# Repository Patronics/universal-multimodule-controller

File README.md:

# Universal Multi-Module Controller

This project aims to allow standard input devices (such as game controllers and keyboards) to control output to 4-in-one multi-module transmitters.

Created by Patrick Leiser and Josh Adriano.

## Installation
Use the [Arduino-Pico board core](https://arduino-pico.readthedocs.io/en/latest/) by Earle Philhower
Dependencies:
U8g2 by oliver
ArduinoJson by Benoit Blanchon
Bounce2 by Thomas O Fredericks
Pico PIO USB by Sekigon-gonnoc

You can program it with the Arduino IDE directly, adjust the menu options as described at the top of `GamesteerRC.ino`.

Alternatively, for advanced usage and debugging, you can install the [Arduino-CLI](https://docs.arduino.cc/arduino-cli/) and use the scripts as described below: 

## Build & Debug Scripts

---

### build.sh  
Builds a **release version** of the firmware using Arduino CLI.

- Optimized for performance (`-O2` / `-Os`)
- Produces `.elf` and `.uf2` in `build/`
- Use when you want final or production-like firmware

---

### debug-build.sh  
Builds a **debug version** of the firmware.

- Uses `-Og` optimization for good debugging behavior
- Includes full debug symbols (`-g`)
- Outputs to `build-debug/`
- Use when stepping through code or inspecting variables with GDB

---

### flash.sh  
Flashes firmware using the **Raspberry Pi Debug Probe (OpenOCD + SWD)**.

- Programs the `.elf` directly to flash
- Verifies and resets the device
- Use for fast iteration during debugging

---

### openocd.sh  
Starts the **OpenOCD GDB server**.

- Provides a debugging connection on port 3333
- Required before connecting GDB
- Use when preparing a debug session

---

### gdb.sh  
Launches **GDB for source-level debugging**.

- Connects to OpenOCD (`localhost:3333`)
- Uses the project `.elf`
- Use for breakpoints, stepping, and inspecting state
- See debugging section below for additional details
---

### upload.sh  
Flashes firmware using the **UF2 bootloader (USB mode)**.
- uses `arduino-cli upload`
- Before use, edit upload.sh with the port of your target device, such as `/dev/cu.usbmodem101` or `COM7`
  - Alternatively, you can manually boot the device into BOOTSEL mode, and copy `build/GamesteerRC.ino.uf2` onto the device.
- No debugger needed
- Use for simple deployment or recovery
---

### Typical usage
Call the scripts from the top level of the directory, such as `./scripts/build.sh`
- **Development (debugging):** `debug-build.sh` → `flash.sh` → `openocd.sh` → *(in a second terminal session)* `gdb.sh`
- **Quick standalone flash:** `build.sh → upload.sh`

## Debugging
For debugging, once OpenOCD and GDB are active, within GDB run 
```gdb
target extended-remote :3333
monitor reset halt
break panic
continue

```

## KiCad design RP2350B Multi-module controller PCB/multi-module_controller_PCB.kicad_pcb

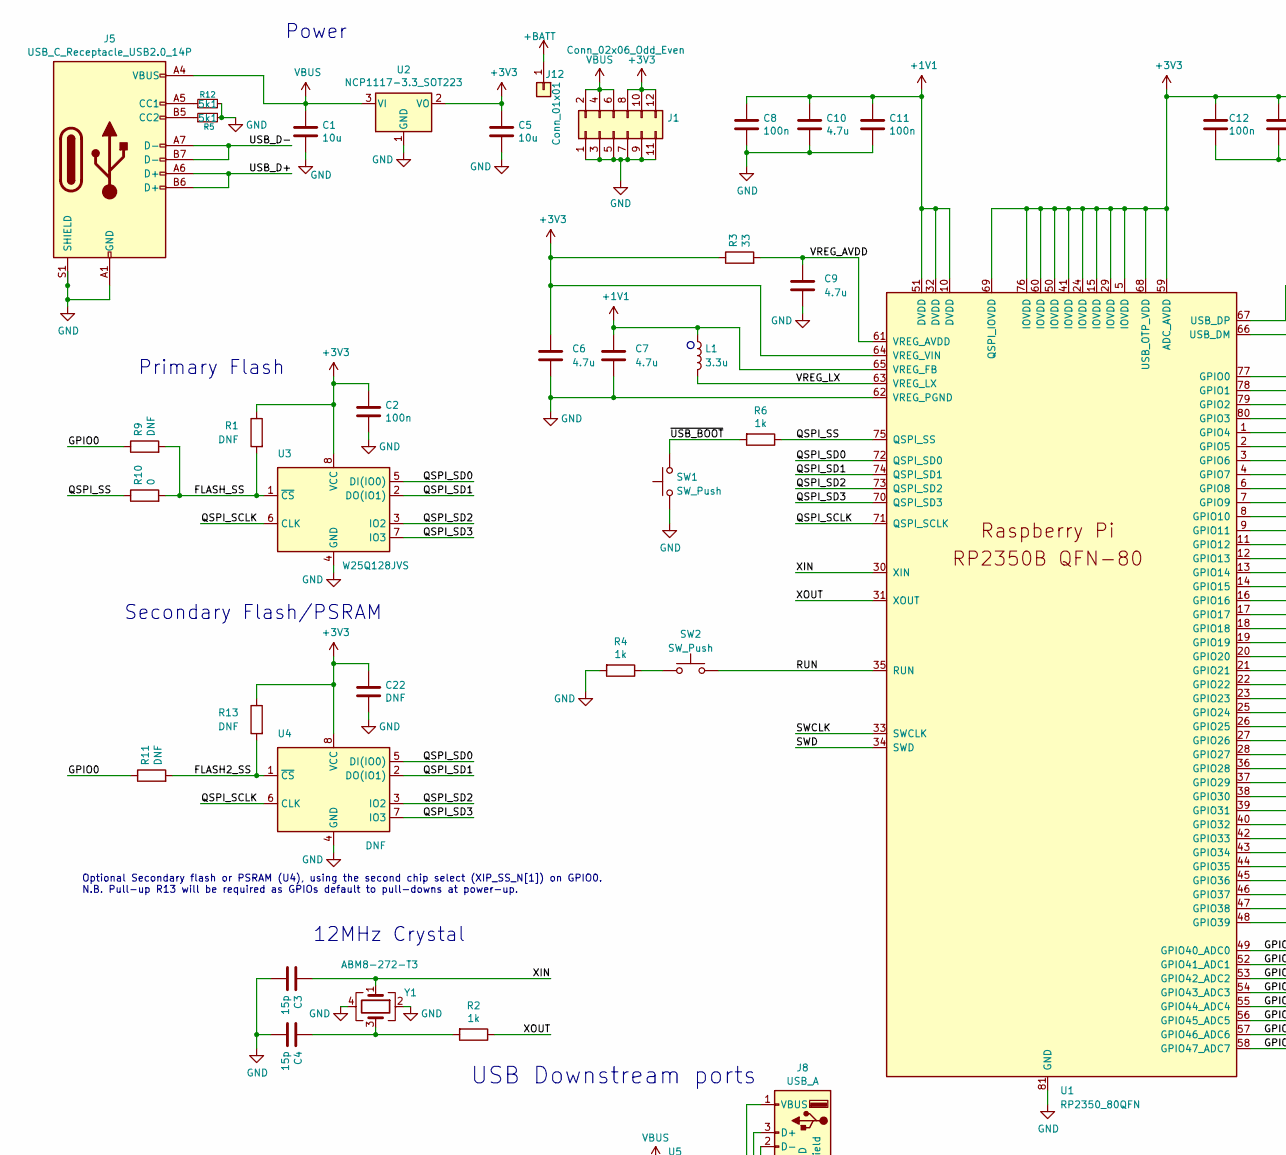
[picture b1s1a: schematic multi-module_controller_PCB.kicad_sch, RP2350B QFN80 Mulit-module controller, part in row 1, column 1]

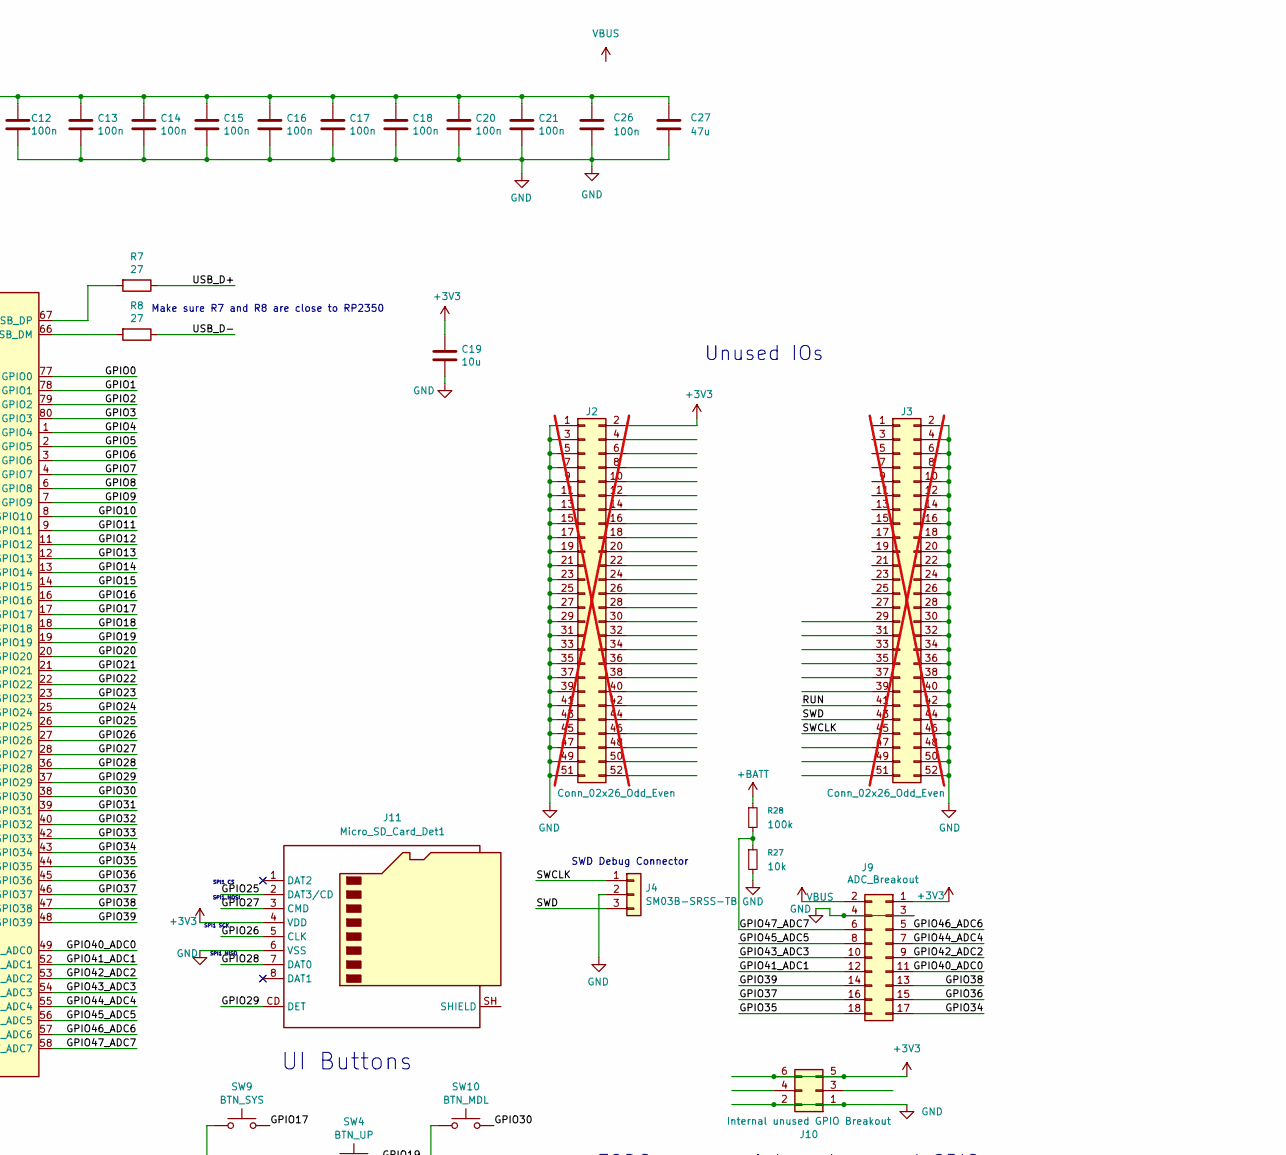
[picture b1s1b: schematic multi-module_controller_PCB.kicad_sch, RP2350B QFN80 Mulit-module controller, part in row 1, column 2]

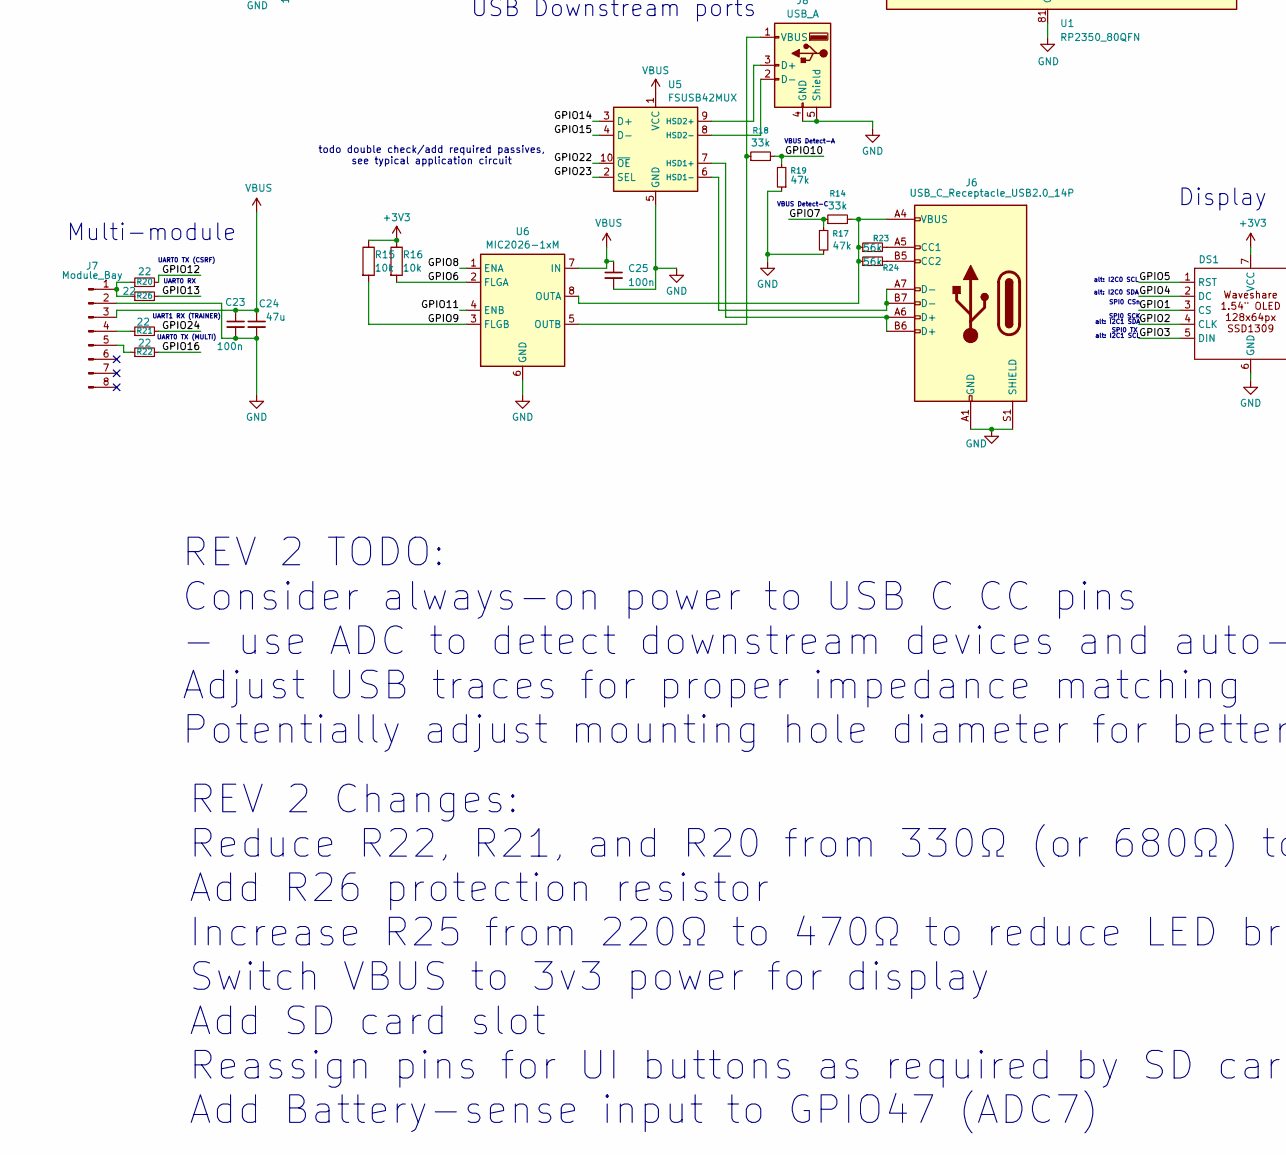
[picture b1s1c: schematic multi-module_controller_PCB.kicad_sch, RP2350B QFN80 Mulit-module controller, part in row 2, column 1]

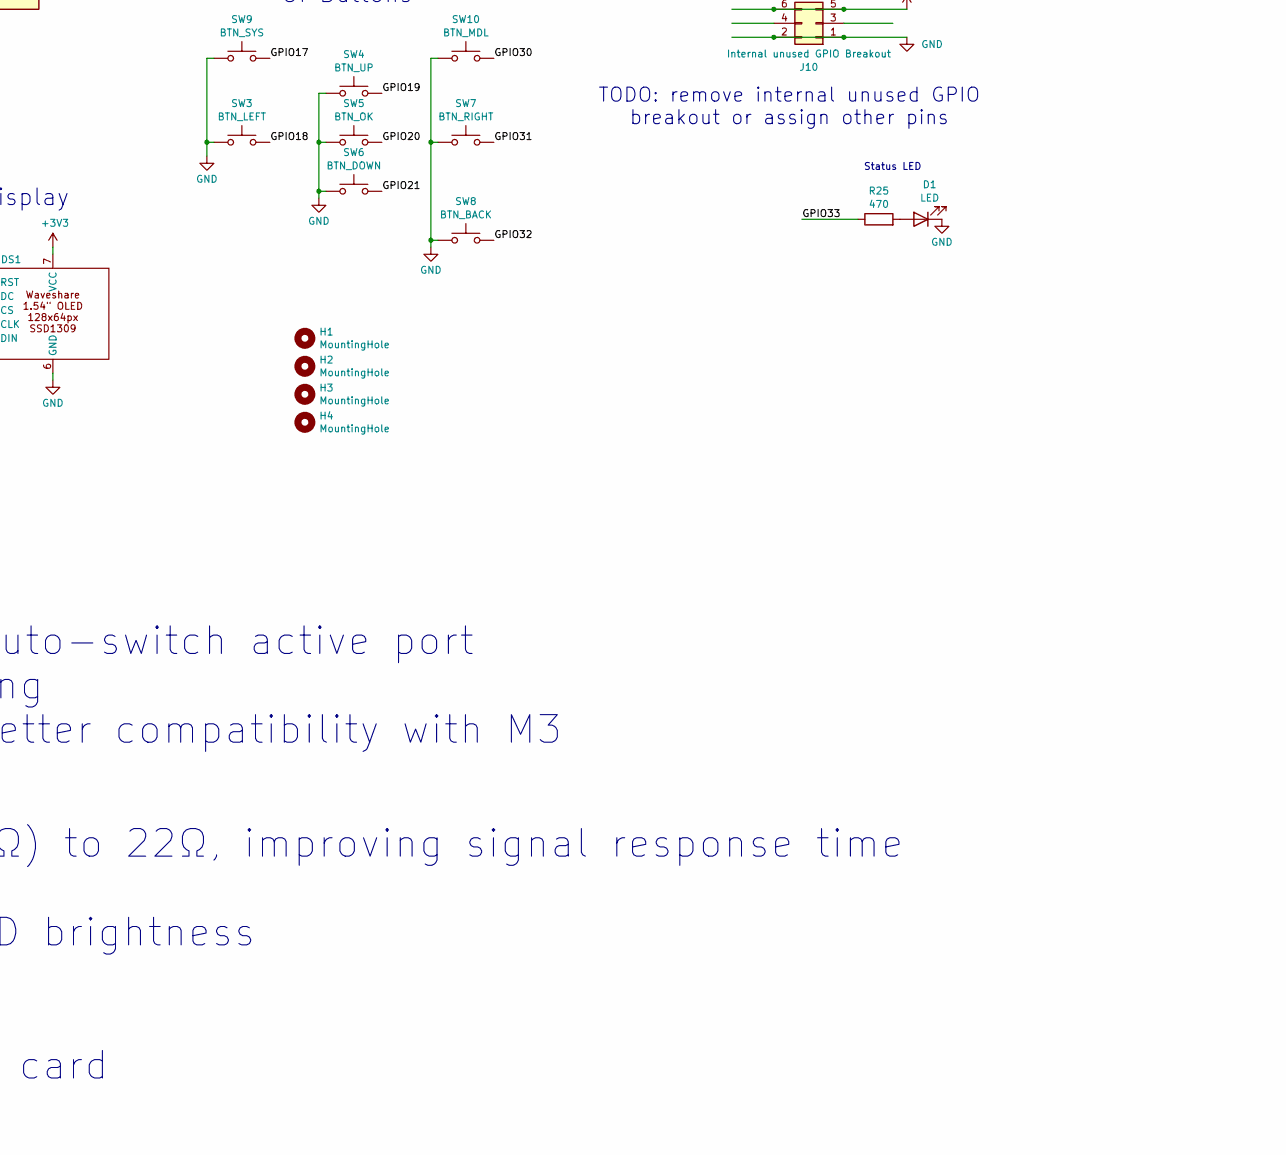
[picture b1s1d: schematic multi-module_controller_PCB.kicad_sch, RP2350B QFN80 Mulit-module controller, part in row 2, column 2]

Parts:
C1, C5, C19: 10u; C_0805_2012Metric; LCSC C15850
C2, C8, C11, C12, C13, C14, C15, C16, C17, C18, C20, C21, C23, C25: 100n; C_0402_1005Metric; LCSC C1525
C3, C4: 15p; C_0402_1005Metric; LCSC C7467172
C6, C7: 4.7u; C_0402_1005Metric_small_pads; LCSC C23733
C9, C10: 4.7u; C_0402_1005Metric; LCSC C23733
C22: DNF; C_0402_1005Metric
C24: 47u; C_1206_3216Metric; LCSC C16780
C26: 100n; C_0402_1005Metric
C27: 47u; C_1206_3216Metric
D1: LED; LED_0603_1608Metric; LCSC C7496818
DS1: Waveshare 1.54in OLED
H1, H2, H3, H4: MountingHole; MountingHole_3.2mm_M3
J1: Conn_02x06_Odd_Even; PinSocket_2x06_P2.54mm_Vertical
J2, J3: Conn_02x26_Odd_Even; PinHeader_2x26_P2.54mm_Vertical; not fitted
J4: SM03B-SRSS-TB; PinHeader_1x03_P2.54mm_Vertical
J5, J6: USB_C_Receptacle_USB2.0_14P; USB_C_Receptacle_G-Switch_GT-USB-7010ASV; LCSC C2988369
J7: Module_Bay; PinHeader_1x08_P2.54mm_Vertical; LCSC C19184340
J8: USB_A; USB_A_Connfly_DS1095; LCSC C456018
J9: ADC_Breakout; PinHeader_2x09_P2.54mm_Vertical
J10: Internal unused GPIO Breakout; PinHeader_2x03_P1.27mm_Vertical
J11: Micro_SD_Card_Det1; SD-SMD_MLD-TF-PUSH-H18
J12: Conn_01x01; PinHeader_1x01_P2.54mm_Vertical
L1: 3.3u; L_pol_2016; LCSC C42411119
R1, R9, R11, R13: DNF; R_0402_1005Metric
R2, R4, R6: 1k; R_0402_1005Metric; LCSC C11702
R3: 33; R_0402_1005Metric; LCSC C25105
R5, R12: 5k1; R_0402_1005Metric; LCSC C25905
R7, R8: 27; R_0402_1005Metric; LCSC C25100
R10: 0; R_0402_1005Metric; LCSC C17168
R14, R18: 33k; R_0402_1005Metric; LCSC C25744
R15, R16: 10k; R_0402_1005Metric; LCSC C25744
R17, R19: 47k; R_0402_1005Metric; LCSC C25792
R20, R26: 22; R_0402_1005Metric; LCSC C25130
R21, R22: 22; R_0402_1005Metric; LCSC C25104
R23, R24: 56k; R_0402_1005Metric; LCSC C2906875
R25: 470; R_0603_1608Metric; LCSC C22962
R27: 10k; R_0402_1005Metric
R28: 100k; R_0402_1005Metric
SW1, SW2: SW_Push; SW_Push_1P1T_NO_Vertical_Wuerth_434133025816; LCSC C2910644
SW3: BTN_LEFT; SW_Push_1P1T_NO_E-Switch_TL3301NxxxxxG; LCSC C2837532
SW4: BTN_UP; SW_Push_1P1T_NO_E-Switch_TL3301NxxxxxG; LCSC C2837532
SW5: BTN_OK; SW_Push_1P1T_NO_E-Switch_TL3301NxxxxxG; LCSC C2837532
SW6: BTN_DOWN; SW_Push_1P1T_NO_E-Switch_TL3301NxxxxxG; LCSC C2837532
SW7: BTN_RIGHT; SW_Push_1P1T_NO_E-Switch_TL3301NxxxxxG; LCSC C2837532
SW8: BTN_BACK; SW_Push_1P1T_NO_E-Switch_TL3301NxxxxxG; LCSC C2837532
SW9: BTN_SYS; SW_Push_1P1T_NO_E-Switch_TL3301NxxxxxG; LCSC C2837532
SW10: BTN_MDL; SW_Push_1P1T_NO_E-Switch_TL3301NxxxxxG; LCSC C2837532
U1: RP2350_80QFN; RP2350-QFN-80-1EP_10x10_P0.4mm_EP3.4x3.4mm_ThermalVias; LCSC C42415655
U2: NCP1117-3.3_SOT223; SOT-223-3_TabPin2; LCSC C88234
U3: W25Q128JVS; SOIC-8_5.23x5.23mm_P1.27mm; LCSC C97521
U4: DNF; SOIC-8_5.23x5.23mm_P1.27mm
U5: FSUSB42MUX; MSOP-10_3x3mm_P0.5mm; LCSC C11355
U6: MIC2026-1xM; SOIC-8_3.9x4.9mm_P1.27mm; LCSC C144190
Y1: ABM8-272-T3; Crystal_SMD_3225-4Pin_3.2x2.5mm; LCSC C20625731

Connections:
+1V1: C7.1, C8.1, C10.1, C11.1, L1.1, U1.10 (DVDD), U1.32 (DVDD), U1.51 (DVDD), U1.65 (VREG_FB)
+3V3: C2.1, C5.1, C6.1, C12.1, C13.1, C14.1, C15.1, C16.1, C17.1, C18.1, C19.1, C20.1, C21.1, C22.1, C26.1, C27.1, DS1.7 (VCC), J1.8, J1.10, J1.12, J2.2, J9.1, J10.5, J10.6, J11.4 (VDD), R1.1, R3.1, R13.1, R15.1, R16.1, U1.5 (IOVDD), U1.15 (IOVDD), U1.24 (IOVDD), U1.29 (IOVDD), U1.41 (IOVDD), U1.50 (IOVDD), U1.59 (ADC_AVDD), U1.60 (IOVDD), U1.64 (VREG_VIN), U1.68 (USB_OTP_VDD), U1.69 (QSPI_IOVDD), U1.76 (IOVDD), U2.2 (VO), U3.8 (VCC), U4.8 (VCC)
+BATT: J12.1 (Pin_1_1), R28.1
/FLASH2_SS: R11.2, R13.2, U4.1 (~CS)
/FLASH_SS: R1.2, R9.2, R10.2, U3.1 (~CS)
/GPIO0: R9.1, R11.1, U1.77 (GPIO0)
/GPIO1: DS1.3 (CS), U1.78 (GPIO1)
/GPIO2: DS1.4 (CLK), U1.79 (GPIO2)
/GPIO3: DS1.5 (DIN), U1.80 (GPIO3)
/GPIO4: DS1.2 (DC), U1.1 (GPIO4)
/GPIO5: DS1.1 (RST), U1.2 (GPIO5)
/GPIO6: R16.2, U1.3 (GPIO6), U6.2 (FLGA)
/GPIO7: R14.1, R17.1, U1.4 (GPIO7)
/GPIO8: U1.6 (GPIO8), U6.1 (ENA)
/GPIO9: R15.2, U1.7 (GPIO9), U6.3 (FLGB)
/GPIO10: R18.2, R19.2, U1.8 (GPIO10)
/GPIO11: U1.9 (GPIO11), U6.4 (ENB)
/GPIO12: R20.2, U1.11 (GPIO12)
/GPIO13: R26.2, U1.12 (GPIO13)
/GPIO14: U1.13 (GPIO14), U5.3 (D+)
/GPIO15: U1.14 (GPIO15), U5.4 (D-)
/GPIO16: R22.2, U1.16 (GPIO16)
/GPIO17: SW9.2, U1.17 (GPIO17)
/GPIO18: SW3.2, U1.18 (GPIO18)
/GPIO19: SW4.2, U1.19 (GPIO19)
/GPIO20: SW5.2, U1.20 (GPIO20)
/GPIO21: SW6.2, U1.21 (GPIO21)
/GPIO22: U1.22 (GPIO22), U5.10 (~OE)
/GPIO23: U1.23 (GPIO23), U5.2 (SEL)
/GPIO24: R21.2, U1.25 (GPIO24)
/GPIO25: J11.2 (DAT3/CD), U1.26 (GPIO25)
/GPIO26: J11.5 (CLK), U1.27 (GPIO26)
/GPIO27: J11.3 (CMD), U1.28 (GPIO27)
/GPIO28: J11.7 (DAT0), U1.36 (GPIO28)
/GPIO29: J11.CD (DET), U1.37 (GPIO29)
/GPIO30: SW10.2, U1.38 (GPIO30)
/GPIO31: SW7.2, U1.39 (GPIO31)
/GPIO32: SW8.2, U1.40 (GPIO32)
/GPIO33: R25.1, U1.42 (GPIO33)
/GPIO34: J9.17, U1.43 (GPIO34)
/GPIO35: J9.18, U1.44 (GPIO35)
/GPIO36: J9.15, U1.45 (GPIO36)
/GPIO37: J9.16, U1.46 (GPIO37)
/GPIO38: J9.13, U1.47 (GPIO38)
/GPIO39: J9.14, U1.48 (GPIO39)
/GPIO40_ADC0: J9.11, U1.49 (GPIO40_ADC0)
/GPIO41_ADC1: J9.12, U1.52 (GPIO41_ADC1)
/GPIO42_ADC2: J9.9, U1.53 (GPIO42_ADC2)
/GPIO43_ADC3: J9.10, U1.54 (GPIO43_ADC3)
/GPIO44_ADC4: J9.7, U1.55 (GPIO44_ADC4)
/GPIO45_ADC5: J9.8, U1.56 (GPIO45_ADC5)
/GPIO46_ADC6: J9.5, U1.57 (GPIO46_ADC6)
/GPIO47_ADC7: J9.6, R27.1, R28.2, U1.58 (GPIO47_ADC7)
/QSPI_SCLK: U1.71 (QSPI_SCLK), U3.6 (CLK), U4.6 (CLK)
/QSPI_SD0: U1.72 (QSPI_SD0), U3.5 (DI(IO0)), U4.5 (DI(IO0))
/QSPI_SD1: U1.74 (QSPI_SD1), U3.2 (DO(IO1)), U4.2 (DO(IO1))
/QSPI_SD2: U1.73 (QSPI_SD2), U3.3 (IO2), U4.3 (IO2)
/QSPI_SD3: U1.70 (QSPI_SD3), U3.7 (IO3), U4.7 (IO3)
/QSPI_SS: R6.1, R10.1, U1.75 (QSPI_SS)
/RUN: J3.41, SW2.2, U1.35 (RUN)
/SWCLK: J3.45, J4.1, U1.33 (SWCLK)
/SWD: J3.43, J4.3, U1.34 (SWD)
/USB_D+: J5.A6 (D+), J5.B6 (D+), R7.1
/USB_D-: J5.A7 (D-), J5.B7 (D-), R8.1
/VREG_AVDD: C9.1, R3.2, U1.61 (VREG_AVDD)
/VREG_LX: L1.2, U1.63 (VREG_LX)
/XIN: C3.1, U1.30 (XIN), Y1.1
/XOUT: R2.1, U1.31 (XOUT)
/~USB_BOOT: R6.2, SW1.2
GND: C1.2, C2.2, C3.2, C4.2, C5.2, C6.2, C7.2, C8.2, C9.2, C10.2, C11.2, C12.2, C13.2, C14.2, C15.2, C16.2, C17.2, C18.2, C19.2, C20.2, C21.2, C22.2, C23.2, C24.2, C25.2, C26.2, C27.2, D1.1 (K), DS1.6 (GND), J1.1, J1.3, J1.5, J1.7, J1.9, J1.11, J2.1, J2.3, J2.5, J2.7, J2.9, J2.11, J2.13, J2.15, J2.17, J2.19, J2.21, J2.23, J2.25, J2.27, J2.29, J2.31, J2.33, J2.35, J2.37, J2.39, J2.41, J2.43, J2.45, J2.47, J2.49, J2.51, J3.2, J3.4, J3.6, J3.8, J3.10, J3.12, J3.14, J3.16, J3.18, J3.20, J3.22, J3.24, J3.26, J3.28, J3.30, J3.32, J3.34, J3.36, J3.38, J3.40, J3.42, J3.44, J3.46, J3.48, J3.50, J3.52, J4.2, J5.A1 (GND), J5.A12 (GND), J5.B1 (GND), J5.B12 (GND), J5.S1 (SHIELD), J6.A1 (GND), J6.A12 (GND), J6.B1 (GND), J6.B12 (GND), J6.S1 (SHIELD), J7.2, J8.4 (GND), J8.5 (Shield), J9.3, J9.4, J10.1, J10.2, J11.6 (VSS), R4.2, R5.2, R12.2, R17.2, R19.1, R27.2, SW1.1, SW3.1, SW4.1, SW5.1, SW6.1, SW7.1, SW8.1, SW9.1, SW10.1, U1.62 (VREG_PGND), U1.81 (GND), U2.1 (GND), U3.4 (GND), U4.4 (GND), U5.5 (GND), U6.6 (GND), Y1.2, Y1.4
unnamed: C4.1, R2.2, Y1.3
unnamed: D1.2 (A), R25.2
unnamed: J5.A5 (CC1), R12.1
unnamed: J5.B5 (CC2), R5.1
unnamed: J6.A5 (CC1), R23.2
unnamed: J6.B5 (CC2), R24.2
unnamed: J7.1, R20.1, R26.1
unnamed: J7.4, R21.1
unnamed: J7.5, R22.1
unnamed: J8.3 (D+), U5.9 (HSD2+)
unnamed: J8.2 (D-), U5.8 (HSD2-)
unnamed: J8.1 (VBUS), R18.1, U6.5 (OUTB)
unnamed: R4.1, SW2.1
unnamed: R8.2, U1.66 (USB_DM)
unnamed: R7.2, U1.67 (USB_DP)
unnamed: J6.A6 (D+), J6.B6 (D+), U5.7 (HSD1+)
unnamed: J6.A7 (D-), J6.B7 (D-), U5.6 (HSD1-)
unnamed: J6.A4 (VBUS), J6.A9 (VBUS), J6.B4 (VBUS), J6.B9 (VBUS), R14.2, R23.1, R24.1, U6.8 (OUTA)
VBUS: C1.1, C23.1, C24.1, C25.1, J1.2, J1.4, J1.6, J5.A4 (VBUS), J5.A9 (VBUS), J5.B4 (VBUS), J5.B9 (VBUS), J7.3, J9.2, U2.3 (VI), U5.1 (VCC), U6.7 (IN)

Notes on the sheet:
Optional Secondary flash or PSRAM (U4), using the second chip select (XIP_SS_N[1]) on GPIO0. N.B. Pull-up R13 will be required as GPIOs default to pull-downs at power-up.
REV 2 TODO: Consider always-on power to USB C CC pins - use ADC to detect downstream devices and auto-switch active port Adjust USB traces for proper impedance matching Potentially adjust mounting hole diameter for better compatibility with M3
Unused IOs
12MHz Crystal
SPI0 SCK
SPI1 SCK
alt: I2C0 SCL
UART0 TX (CSRF)
VBUS Detect-C
UART0 TX (MULTI)
SPI1 CS
Multi-module
UI Buttons
Status LED
Primary Flash
SPI1 MOSI
alt: I2C1 SCL
REV 2 Changes: Reduce R22, R21, and R20 from 330Ω (or 680Ω) to 22Ω, improving signal response time Add R26 protection resistor Increase R25 from 220Ω to 470Ω to reduce LED brightness Switch VBUS to 3v3 power for display Add SD card slot Reassign pins for UI buttons as required by SD card Add Batter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
USB Downstream ports
todo double check/add required passives, see typical application circuit
SWD Debug Connector
UART1 RX (TRAINER)
TODO: remove internal unused GPIO breakout or assign other pins
Make sure R7 and R8 are close to RP2350
VBUS Detect-A
Secondary Flash/PSRAM
Display
alt: I2C0 SDA
UART0 RX
alt: I2C1 SDA
Power
SPI0 CSn
SPI0 TX
SPI1 MISO

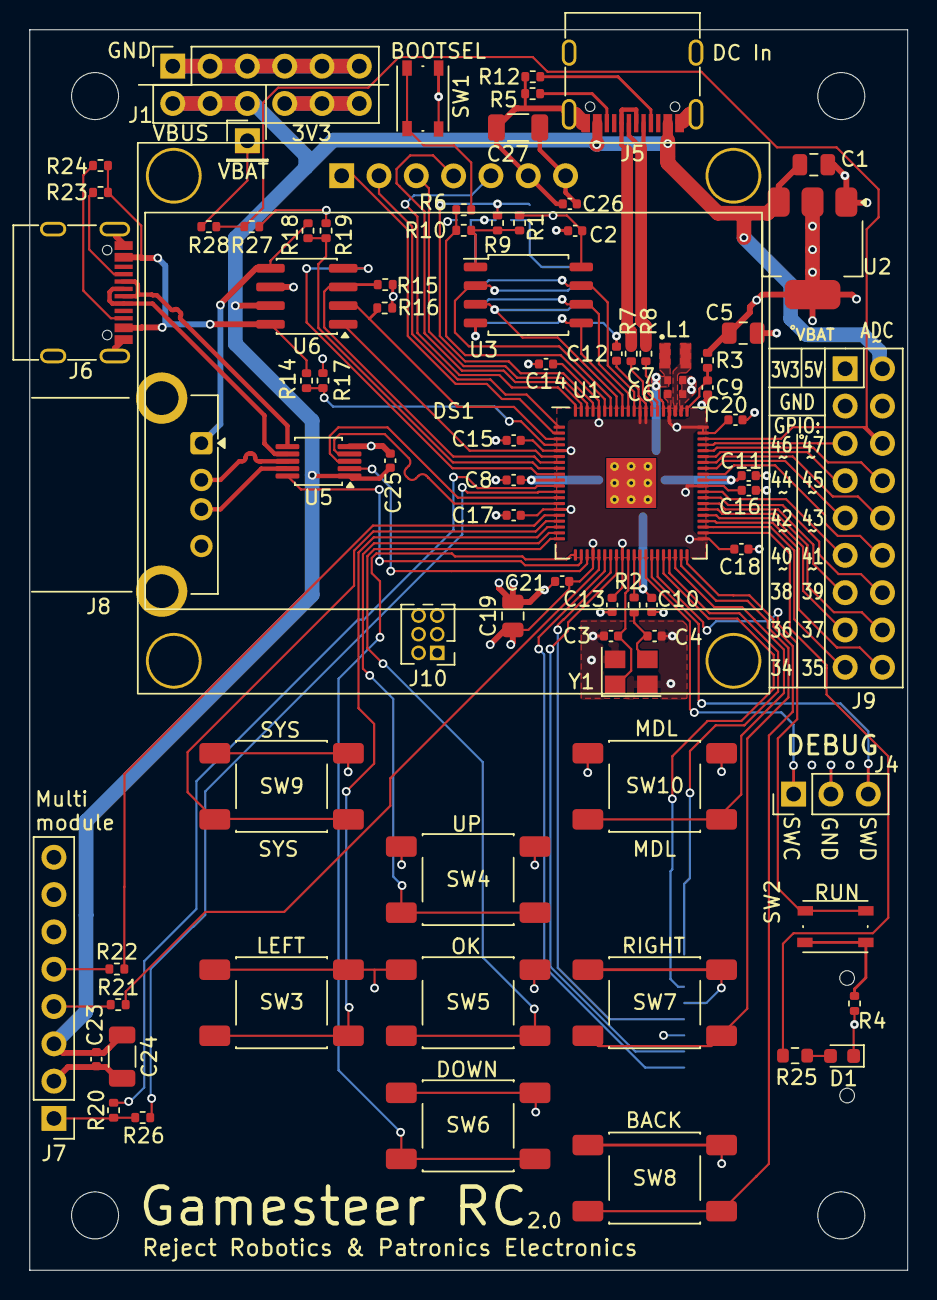
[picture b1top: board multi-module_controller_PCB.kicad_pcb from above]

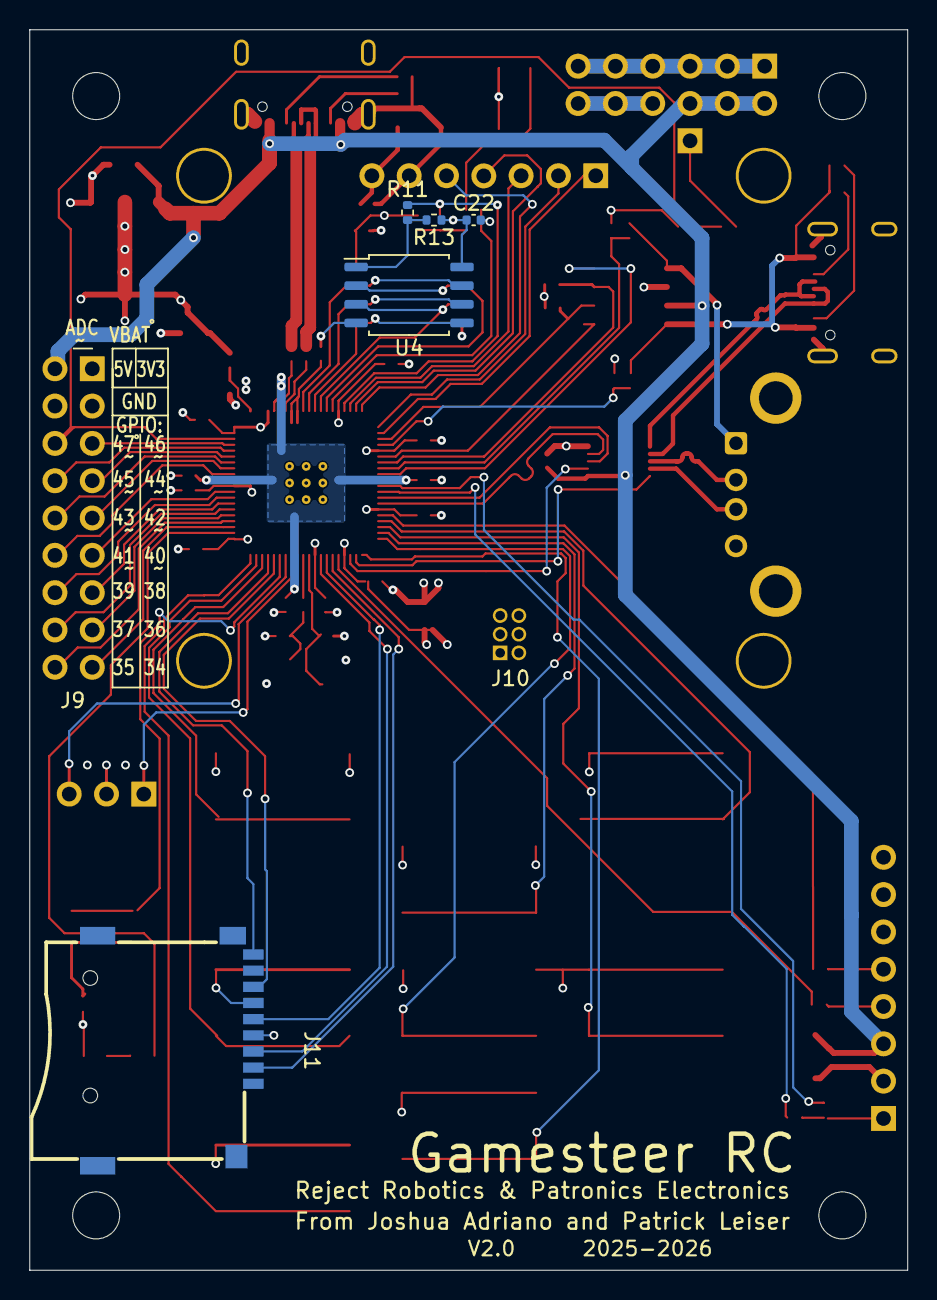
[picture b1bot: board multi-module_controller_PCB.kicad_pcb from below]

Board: 4 copper layers, 59.8 x 84.4 mm, 89 parts (5 on the bottom side), 89 nets.

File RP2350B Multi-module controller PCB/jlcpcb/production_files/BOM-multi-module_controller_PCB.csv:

Comment,Designator,Footprint,LCSC,Quantity
0,R10,R_0402_1005Metric,C17168,1
0.1u,C25,C_0402_1005Metric,C1525,1
100n,"C11,C12,C13,C14,C15,C16,C17,C18,C2,C20,C21,C23,C26,C8",C_0402_1005Metric,C1525,14
10k,"R15,R16",R_0402_1005Metric,C25744,2
10u,"C1,C19,C5",C_0805_2012Metric,C15850,3
15p,"C3,C4",C_0402_1005Metric,C7467172,2
1k,"R2,R4,R6",R_0402_1005Metric,C11702,3
22,"R20,R21,R22,R26",R_0402_1005Metric,C25092,4
27,"R7,R8",R_0402_1005Metric,C25100,2
3.3u,L1,L_pol_2016,C42411119,1
33,R3,R_0402_1005Metric,C25105,1
33k,"R14,R18",R_0402_1005Metric,C25779,2
4.7u,"C10,C6,C7,C9",C_0402_1005Metric,C23733,4
470,R25,R_0603_1608Metric,C23179,1
47k,"R17,R19",R_0402_1005Metric,C25792,2
47u,"C24,C27",C_1206_3216Metric,C96123,2
56k,"R23,R24",R_0402_1005Metric,C2906875,2
5k1,"R12,R5",R_0402_1005Metric,C25905,2
ABM8-272-T3,Y1,Crystal_SMD_3225-4Pin_3.2x2.5mm,C20625731,1
BTN_BACK,SW8,SW_Push_1P1T_NO_E-Switch_TL3301NxxxxxG,C2837532,1
BTN_DOWN,SW6,SW_Push_1P1T_NO_E-Switch_TL3301NxxxxxG,C2837532,1
BTN_LEFT,SW3,SW_Push_1P1T_NO_E-Switch_TL3301NxxxxxG,C2837532,1
BTN_MDL,SW10,SW_Push_1P1T_NO_E-Switch_TL3301NxxxxxG,C2837532,1
BTN_OK,SW5,SW_Push_1P1T_NO_E-Switch_TL3301NxxxxxG,C2837532,1
BTN_RIGHT,SW7,SW_Push_1P1T_NO_E-Switch_TL3301NxxxxxG,C2837532,1
BTN_SYS,SW9,SW_Push_1P1T_NO_E-Switch_TL3301NxxxxxG,C2837532,1
BTN_UP,SW4,SW_Push_1P1T_NO_E-Switch_TL3301NxxxxxG,C2837532,1
FSUSB42MUX,U5,MSOP-10_3x3mm_P0.5mm,C11355,1
LED,D1,LED_0603_1608Metric,C7496818,1
MIC2026-1xM,U6,SOIC-8_3.9x4.9mm_P1.27mm,C144190,1
Module_Bay,J7,PinHeader_1x08_P2.54mm_Vertical,C19184340,1
NCP1117-3.3_SOT223,U2,SOT-223-3_TabPin2,C88234,1
RP2350_80QFN,U1,RP2350-QFN-80-1EP_10x10_P0.4mm_EP3.4x3.4mm_ThermalVias,C42415655,1
SW_Push,"SW1,SW2",SW_Push_1P1T_NO_Vertical_Wuerth_434133025816,C2910644,2
USB_A,J8,USB_A_Connfly_DS1095,C456018,1
USB_C_Receptacle_USB2.0_14P,"J5,J6",USB_C_Receptacle_G-Switch_GT-USB-7010ASV,C2988369,2
W25Q128JVS,U3,SOIC-8_5.23x5.23mm_P1.27mm,C97521,1
~,DS1,Waveshare 1.54in OLED,,1
SM03B-SRSS-TB,J4,PinHeader_1x03_P2.54mm_Vertical,,1
DNF,R1,R_0402_1005Metric,,1
MountingHole,H2,MountingHole_2.7mm_M2.5,,1
MountingHole,H3,MountingHole_2.7mm_M2.5,,1
MountingHole,H1,MountingHole_2.7mm_M2.5,,1
MountingHole,H4,MountingHole_2.7mm_M2.5,,1
DNF,R9,R_0402_1005Metric,,1
DNF,U4,SOIC-8_5.23x5.23mm_P1.27mm,,1
DNF,R11,R_0402_1005Metric,,1
DNF,R13,R_0402_1005Metric,,1
DNF,C22,C_0402_1005Metric,,1
ADC_Breakout,J9,PinHeader_2x09_P2.54mm_Vertical,,1
Conn_02x06_Odd_Even,J1,PinSocket_2x06_P2.54mm_Vertical,,1
Internal unused GPIO Breakout,J10,PinHeader_2x03_P1.27mm_Vertical,,1

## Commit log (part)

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2025-10-24 start capturing telemetry data, starting with headers
2025-10-24 Print raw hex data from telemetry gathered
2025-10-24 fully process and display the Multimodule Status Telemetry Values
2025-10-24 Create GPLv2 or later LICENSE
2025-10-25 start on logic for preparing protocol configuration, improve consistiency of struct item names
2025-10-28 integrate U8G2 display library, adjust pin assignment for glowclock board prototyping and improve portability to different hardware, and start displaying status on the display
2025-10-28 add subprotocol and improve text layout
2025-10-28 improve type safety and optimize string printing
2025-10-28 Improve printing reliability, report status when telemetry absent, start handling button inputs, and extend serial buffer to improve reliability
2025-10-28 Extend preparation of outgoing bytes, improve cycle-time when non-telemetry data active, and other misc improvements
2025-10-30 First successful bidirectional communication with multi-module
2025-10-30 implement navigation menu UI
2025-10-30 improve menu selection logic and tracking active/inactive menu status
2025-10-30 Implement protocol picker interface, fully functional for both sub-protocols and full protocols
2025-10-30 add interface to change receiver number and toggle bind and auto-bind flags
2025-11-07 major new feature, channel management UI and data structures, allowing configurable mapping of inputs to outputs. Currently a few default values available
2025-11-07 actually send the configured/received values for each channel
2025-11-08 Add ADC input device descriptor support
2025-11-09 refactoring, lots of changes and improvements, but needs debugging before transferring to main
2025-11-09 improve defaultInputDescriptor format
2025-11-09 pull forward UI logic migration to UI.cpp and UI.h from debug branch
2025-11-09 pull forward additional changes from debug branch, adding AllocConfigValueInput function and improving type safety
2025-11-09 fix assertion of numChannels
2025-11-10 Pull forward remaining changes from debug branch, implementing improved logic for initializing default output values
2025-11-12 correct ADC range and improve fault tolerance for invalid configurations
2025-11-18 minimal POC tinyUSB keyboard input
2025-11-18 Implement USB keyboard number-key input channel, and framework for other USB device handling
2025-11-23 Functional input from PS4 DualShock controller joysticks and triggers
2025-11-24 Replace hardcoded DS4 configuration to instead support arbitrary controllers with simple reconfiguration in controllerData.h. Currently implemented support for analog inputs from Sony DS4, DS5, and 8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
2025-12-05 initial commit of WIP Kicad project for dedicated PCB
2025-12-05 all core components placed and routed
2025-12-05 minor tweaks to USB port overhang positioning
2025-12-18 completed layout, include production files, before adjusting component mounting
2025-12-19 adjust GPIO breakout, add LED, silkscreen labels, etc
2025-12-19 add date to silkscreen
2026-02-11 add hardware tests for new board
2026-02-11 Implement pin-remapping and adjustments for new PCB, add support for both USB A and C ports (configured at compile-time by active_usb_port for now). Buttons, i2c display, USB A, USB C, all functional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
2026-02-12 start on revisions for REV2 board design
2026-02-12 Split main menu into sys and model menus, implement USB port switching menu and functionality, log detailed device descriptor information
2026-02-18 start implementation of filesystem
2026-02-22 Add basic per-model save and load of configuration, starting with protocol, subprotocol, and USB port.
2026-03-13 add FindInputChannelDescriptorByInputNameSuffix() function to allow matching both precise and imprecise names for known input channels
2026-03-13 Enable saving and loading channel maps for models
2026-03-25 Improve cleanup of disconnected USB devices, including assigned output channels.
2026-03-25 start to define mixer data structure
2026-05-07 update software to use SPI LCD at up to 8MHz
2026-05-07 Update PCB with improved bulk capacitors for VBus, increased mounting hole diameter for display, and offset multi-module connector further away from USB A port
2026-05-08 update PCB to drive OLED from 3v3 rail
2026-05-08 Add alternative SPI pinout configurations, rearrange menu, implement sample layout for mixes menu
2026-05-13 start reformat of menu layout to free up more space for submenu display
2026-05-13 add u8g2PrintPadding function to print a 1 pixel padding before/after text to improve readability with highlighted text
2026-05-13 Automatically update relevant menu items (channel mixer, protocol/subprotocol selector) periodically, and start rearranging menus to better utilize newly-available space
2026-05-16 Fix model button menu bug and rearrange mixer menu layout prototype
2026-05-17 extensive reworking and start on implementation of mixer interface, currently allows selecting mix number, operation, and both input sources
2026-05-17 mixes are now fully functional, with a friendly menu interface for editing them
2026-05-21 save mixer fields into config json (leads to config files around 4.2kB per model). Loading of saved mixers not yet implemented
2026-05-29 Replace Serial.print() with new SerialDebug<LOG_LEVEL_FLAG> syntax, allowing easy removal of unneded/excessively verbose serial logging by category.
2026-05-29 progress on loading mixers implementation, add helper function to find channel by name or type/id (depending on type), and improvements to the debug logging handlers
2026-05-29 complete implementation of load/save mixer
2026-05-31 add scripts directory and use arduino-cli to compile boards for ease of automation and debugging
2026-05-31 add CLI build option and documentation on CLU builds and debugging
2026-05-31 Update README.md with additional details on script usage
2026-05-31 Fix double-free bug when deconstructing USB device, add details to readme with debugging steps
2026-05-31 start preparing PCB schematic for SD card in version 1.1
2026-06-01 Add SD Card slot to underside of board, wired for use with SPI1. Reconfigure button pinout and use J10 pins for this purpose
2026-06-04 Add live channel graph view, and improve debugger script
2026-06-04 fully implement failsafe handling, save failsafe values to profiles, send failsafe value to multi-module, and automatically restore failsafe value when USB input lost
2026-06-04 implement failsafe values for mixer when input sources not present
2026-06-04 Add live output graph to channel map view
2026-06-04 add live graph view (including mixer inputs) to channel mapping page
2026-06-05 add mixer options to handle signed inputs, improve consistiency of normalized mixer operations. Add live bar view of mixer values
2026-06-12 Update todo and done details on schematic, start on 3D model for case
